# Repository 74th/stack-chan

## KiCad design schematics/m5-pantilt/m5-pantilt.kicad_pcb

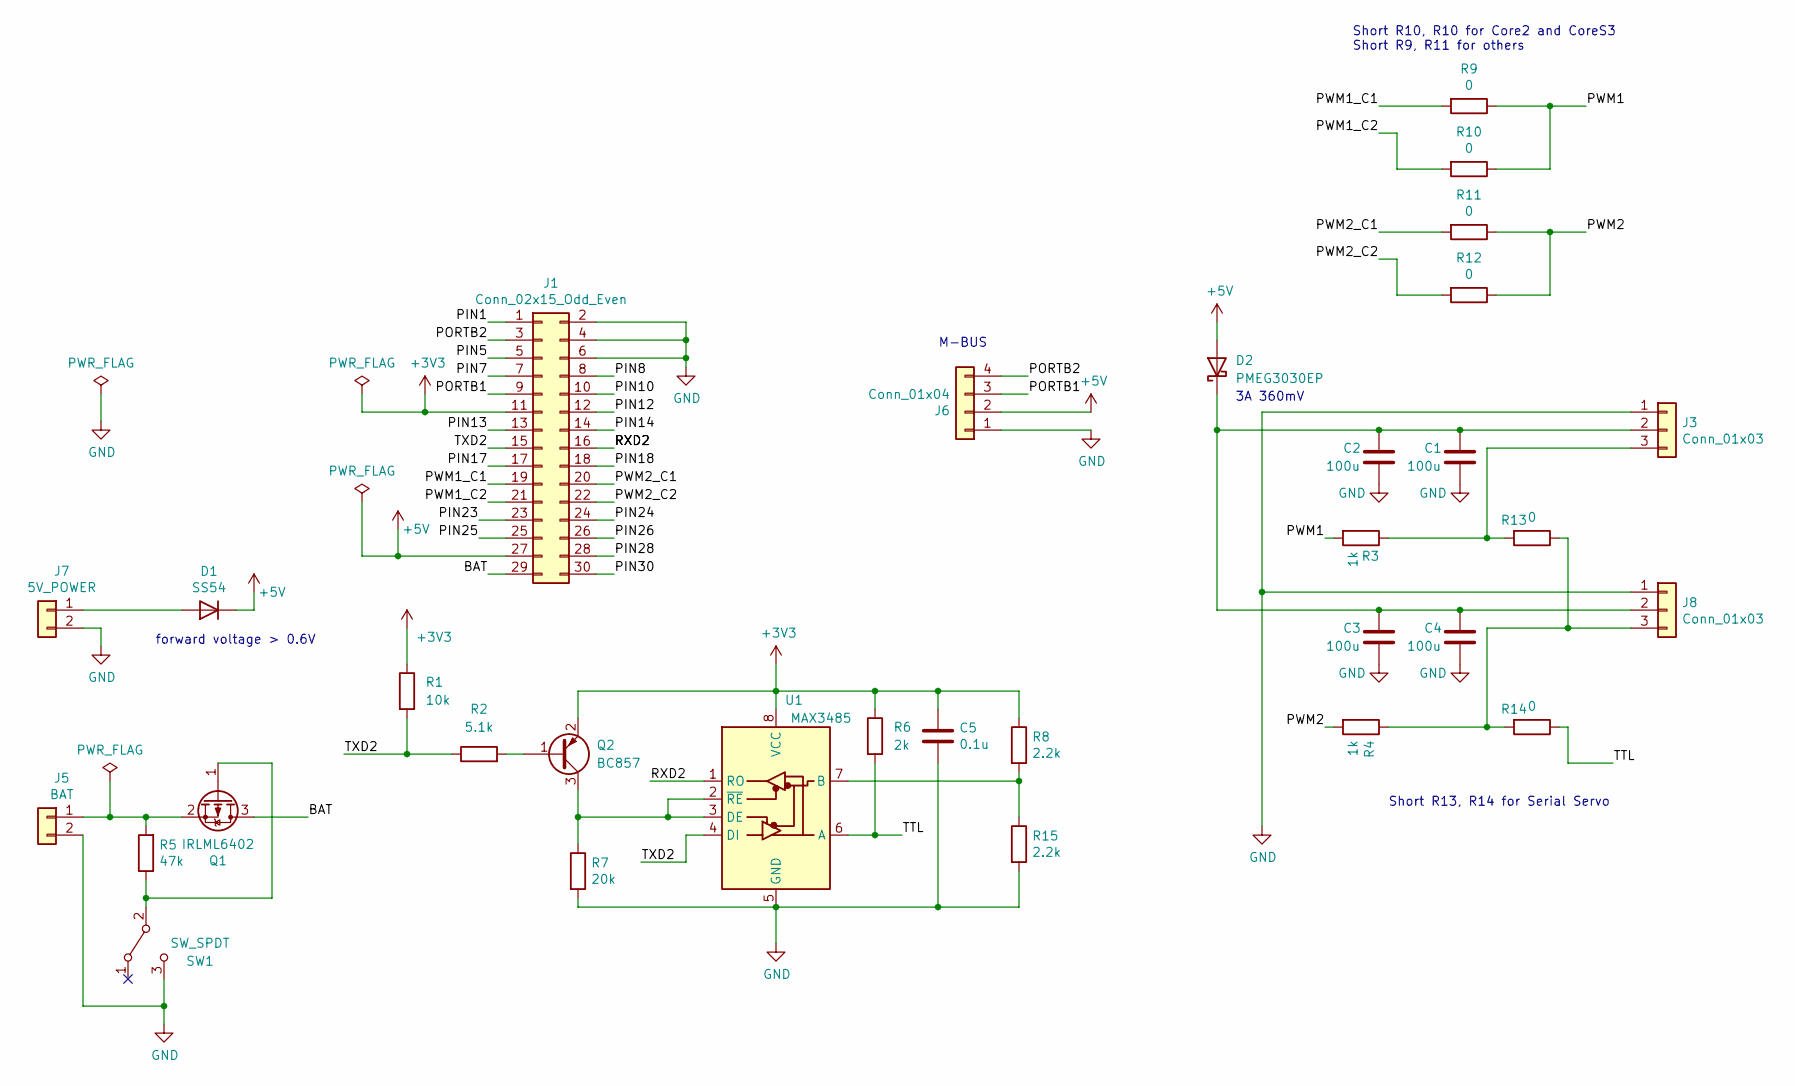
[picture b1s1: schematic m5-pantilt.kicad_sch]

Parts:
C1, C2, C3, C4: 100u; C_1206_3216Metric_Pad1.33x1.80mm_HandSolder; LCSC C15008
C5: 0.1u; C_0603_1608Metric; LCSC C14663
D1: SS54; D_SMA; LCSC C2931790
D2: PMEG3030EP; D_SOD-128; LCSC C255587
J1: Conn_02x15_Odd_Even; PinHeader_2x15_P2.54mm_Vertical_SMD
J3, J8: Conn_01x03; JST_EH_B3B-EH-A_1x03_P2.50mm_Vertical
J5: BAT; JST_PH_B2B-PH-K_1x02_P2.00mm_Vertical; LCSC C2319
J6: Conn_01x04; JST_PH_S4B-PH-K_1x04_P2.00mm_Horizontal
J7: 5V_POWER; JST_XH_B2B-XH-A_1x02_P2.50mm_Vertical; LCSC C20079
Q1: IRLML6402; SOT-23; LCSC C2886430
Q2: BC857; SOT-23; LCSC C2139
R1: 10k; R_0603_1608Metric; LCSC C25804
R2: 5.1k; R_0603_1608Metric; LCSC C23186
R3, R4: 1k; R_0603_1608Metric_Pad0.98x0.95mm_HandSolder; LCSC C21190
R5: 47k; R_0603_1608Metric_Pad0.98x0.95mm_HandSolder; LCSC C25819
R6: 2k; R_0603_1608Metric; LCSC C22975
R7: 20k; R_0603_1608Metric; LCSC C4184
R8, R15: 2.2k; R_0603_1608Metric; LCSC C4190
R9, R10, R11, R12: 0; R_0603_1608Metric_Pad0.98x0.95mm_HandSolder; LCSC C21189
R13, R14: 0; R_0603_1608Metric; LCSC C21189
SW1: SW_SPDT; SW_CuK_OS102011MA1QN1_SPDT_Angled
U1: MAX3485; SO-8_5.3x6.2mm_P1.27mm; LCSC C668204

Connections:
+3V3: C5.1, J1.11, Q2.2 (E), R1.1, R6.1, R8.1, U1.8 (VCC)
+5V: D1.1 (K), D2.2 (A), J1.27, J6.2
/BAT: J1.29, Q1.3 (D)
/PIN1: J1.1
/PIN5: J1.5
/PIN7: J1.7
/PIN8: J1.8
/PIN10: J1.10
/PIN12: J1.12
/PIN13: J1.13
/PIN14: J1.14
/PIN17: J1.17
/PIN18: J1.18
/PIN23: J1.23
/PIN24: J1.24
/PIN25: J1.25
/PIN26: J1.26
/PIN28: J1.28
/PIN30: J1.30
/PORTB1: J1.9, J6.3
/PORTB2: J1.3, J6.4
/PWM1: R3.2, R9.1, R10.1
/PWM1_C1: J1.19, R9.2
/PWM1_C2: J1.21, R10.2
/PWM2: R4.2, R11.1, R12.1
/PWM2_C1: J1.20, R11.2
/PWM2_C2: J1.22, R12.2
/RXD2: J1.16, U1.1 (RO)
/TTL: R6.2, R14.1, U1.6 (A)
/TXD2: J1.15, R1.2, R2.1, U1.4 (DI)
GND: C1.1, C2.1, C3.2, C4.1, C5.2, J1.2, J1.4, J1.6, J3.1, J5.2, J6.1, J7.2, J8.1, R7.2, R15.2, SW1.3 (C), U1.5 (GND)
unnamed: D1.2 (A), J7.1
unnamed: C1.2, C2.2, C3.1, C4.2, D2.1 (K), J3.2, J8.2
unnamed: J3.3, R3.1, R13.2
unnamed: J5.1, Q1.2 (S), R5.2
unnamed: J8.3, R4.1, R13.1, R14.2
unnamed: Q1.1 (G), R5.1, SW1.2 (B)
unnamed: Q2.1 (B), R2.2
unnamed: Q2.3 (C), R7.1, U1.2 (~RE), U1.3 (DE)
unnamed: R8.2, R15.1, U1.7 (B)

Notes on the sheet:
M-BUS
Short R13, R14 for Serial Servo
forward voltage > 0.6V
3A 360mV
Short R10, R10 for Core2 and CoreS3 Short R9, R11 for others

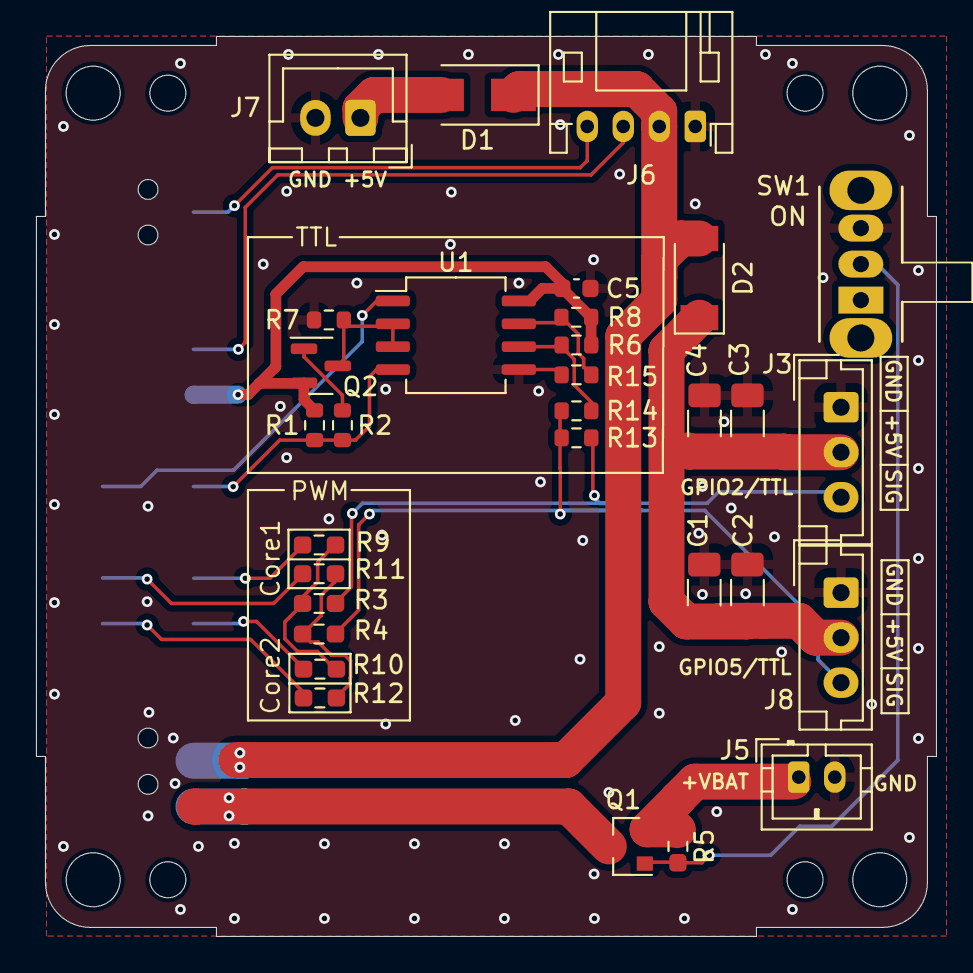
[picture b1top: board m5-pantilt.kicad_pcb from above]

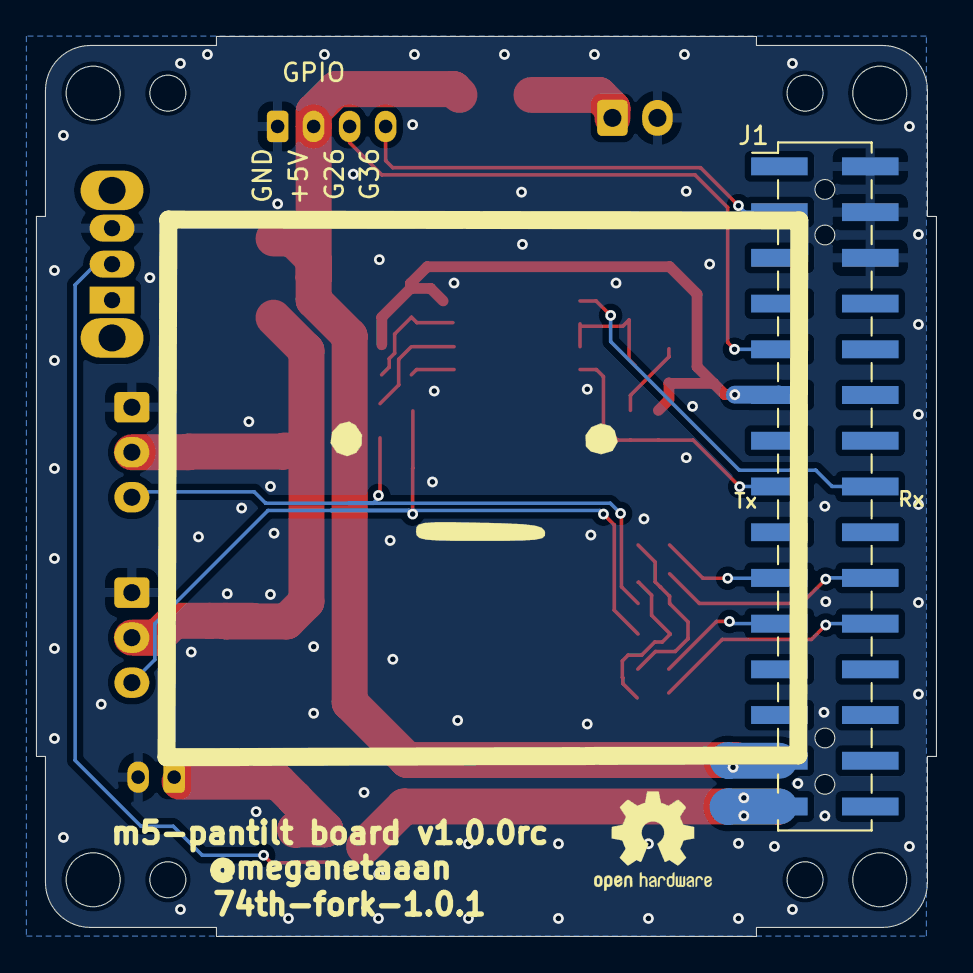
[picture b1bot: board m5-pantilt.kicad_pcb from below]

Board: 2 copper layers, 50.0 x 50.0 mm, 37 parts (2 on the bottom side), 24 nets.

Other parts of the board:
Hole1, Hole2, Hole3, Hole4: mountinghole_M2_M3
LOGO: LOGO; avatar_small

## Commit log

2024-06-17 部品、いくつかのfootprint変更
